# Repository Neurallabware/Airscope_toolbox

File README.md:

<h1 align="center">Airscope</h1>

<p align="center">
  <b>A 1-gram wireless mesoscope for cortex-wide, single-cell-resolution imaging during unrestricted behaviour</b>
</p>

<p align="center">
  <a href="https://airscope.org/devkit/">Device Docs</a> ·
  <a href="https://airscope-docxs.readthedocs.io/en/latest/">Software Docs</a> ·
  <a href="https://drive.google.com/drive/folders/1z9ibX8Ob2NnCdjQDHI7Z4tdhdspn647B?usp=drive_link">Data Release</a>
</p>

---

Airscope is an open hardware and software platform for wireless mesoscopic calcium imaging in freely behaving mice. The device achieves a **6 mm field of view** at ~4 µm lateral resolution, streams or logs **1600 × 1200 px images at 10 Hz**, and weighs approximately **1 g**.

This repository accompanies the manuscript:

> **Deciphering cortex-wide neural dynamics of naturally behaving mice by a 1-gram wireless mesoscope**
> *Zhang et al., Nature, 2025* （Manuscript in preparation）

---

## Repository Structure

| Directory | Description |
|-----------|-------------|
| [`Structure/`](./Structure) | SolidWorks assemblies and part files — housing, baseplate, optical mount, PCB carrier, flexible LED board |
| [`Zemax/`](./Zemax) | Zemax optical design files for the aspheric module |
| [`Electronics/`](./Electronics) | KiCad projects for the main PCB and auxiliary boards |
| [`Firmware/`](./Firmware) | Embedded code for wireless control, camera acquisition, and device configuration |
| [`DAQ_software/`](./DAQ_software) | Python host software and Windows installer for device discovery, preview, and recording |
| [`Software/`](./Software) | Calcium-imaging processing, behavioural segmentation, and neural-decoding pipelines |
| [`Data_release/`](./Data_release) | Example datasets, visualization notebooks, and download instructions |

---

## Key Capabilities

- **Cortex-wide cellular imaging** — 6 mm FOV with single-cell spatial resolution across the dorsal cortex
- **Untethered operation** — wireless data transfer and on-board logging for freely moving, multi-animal, and aquatic paradigms
- **Integrated acquisition stack** — firmware + host software for discovery, preview, timestamping, and recording
- **Reproducible calcium processing** — motion correction → background removal → neuron segmentation → trace extraction
- **Behavioural analysis** — SAM2Mice for multi-animal tracking; Neuron-BERT for decoding social-interaction outcomes

---

## Software Modules

### Calcium-imaging processing · [`Software/Airscope_ca_processing`](./Software/Airscope_ca_processing)

End-to-end pipeline from raw frames to segmented ROI traces. Accepts image sequences, TIFF stacks, and MP4 input; configured with [Hydra](https://hydra.cc) for reproducible batch runs.

```bash
cd Software/Airscope_ca_processing
conda create -n PICO python=3.10 && conda activate PICO
pip install -r requirements.txt && pip install -e .
```

```bash
airscope-process \
  data_path=/path/to/session/frames \
  out_path=/path/to/session/analysis \
  rmbg.gpu_ids=0 rmbg.multi_gpu=false
```

Primary outputs: `seg_results_filtered.mat`, `infer_results_filtered.mat`, `cm_filtered.mat`

---

### SAM2Mice · [`Software/SAM2Mice`](./Software/SAM2Mice)

SAM 2–based mouse segmentation and tracking. Supports manual prompts, YOLOv11 auto-prompts, and bootstrapped inference for videos that exceed GPU memory.

```bash
cd Software/SAM2Mice
pip install torch==2.6.0 torchvision==0.21.0 torchaudio==2.6.0 --index-url https://download.pytorch.org/whl/cu124
pip install -e ".[notebooks]" && python setup.py build_ext --inplace
```

Notebooks in [`Software/SAM2Mice/notebooks_SAM2-MICE`](./Software/SAM2Mice/notebooks_SAM2-MICE) cover basic segmentation, long-video bootstrapping, automatic tracking, and public-dataset examples.

---

### Neuron-BERT · [`Software/Neuron_BERT`](./Software/Neuron_BERT)

Transformer-based decoder for predicting social-interaction outcomes from dual-animal neural activity recordings.

---

### Host acquisition software · [`DAQ_software/`](./DAQ_software)

Dependency-free Python backend — runs without any additional packages:

```bash
cd DAQ_software/airscope_pybackend
python server.py
# UI available at http://127.0.0.1:8765/
```

A packaged Windows installer is also provided at [`DAQ_software/airscope.msi`](./DAQ_software/airscope.msi).

---

## Data Release

Example datasets are hosted on [Google Drive](https://drive.google.com/drive/folders/1z9ibX8Ob2NnCdjQDHI7Z4tdhdspn647B?usp=drive_link) and documented in [`Data_release/README.md`](./Data_release/README.md).
The Google Drive root README is maintained at [`Data_release/README_google_drive.md`](./Data_release/README_google_drive.md) and can be uploaded to Drive as `README_google_drive.md`.

| Dataset | Contents |
|---------|----------|
| Enriched habitat | Calcium traces, multi-view behaviour videos, detection boxes, arena annotations, cortical labels, neuron centroids |
| Multi-animal interaction | Calcium traces, SAM2 instance masks, mouse trajectories, cortical labels, neuron centres |
| MCU timestamp | Frame-rate validation files; use `calculate_frame_rate.ipynb` to verify |
| Optical characterisation | USAF 1951 target images and fluorescent grid slides |

Each dataset directory includes a `README.md` and a `visualize_data.ipynb` notebook.

---

## Requirements

| Component | Environment |
|-----------|-------------|
| Host acquisition software | Python ≥ 3.9, standard library only |
| Calcium processing | Linux, Python 3.10, CUDA-enabled PyTorch recommended |
| SAM2Mice | Python 3.11, PyTorch 2.6.0, CUDA 12.4 |
| Neuron-BERT | Python 3.x, PyTorch, NumPy, scikit-learn, pandas, matplotlib |

See the component-level `README.md` files for exact commands and configuration.

---

## Licensing

Airscope is distributed as a multi-licence repository:

| Material | Licence |
|----------|---------|
| Hardware design (`Structure/`, `Electronics/`, `Zemax/`) | CC-BY-NC-SA-4.0 (commercial use by separate agreement) |
| Software (`DAQ_software/`, `Firmware/`, `Software/`) | GPL-3.0-only |
| Documentation, figures, notebooks, released data | CC-BY-4.0 |

See [`LICENSE`](./LICENSE), [`LICENSES/`](./LICENSES), and [`NOTICE.md`](./NOTICE.md) for the authoritative licence map and third-party notices.

---

## Citation

```bibtex
@article{airscope2025,
  title   = {Deciphering cortex-wide neural dynamics of naturally
             behaving mice by a 1-gram wireless mesoscope},
  author  = {Zhang, Yuanlong and Li, Angran and Yuan, Lekang and
             Wang, Mingrui and Zhao, Weihao and Wang, Zhenbo and
             Zang, Boyang and Zhou, Yangxuan and Yu, Tao and Gao, Lin
             and Wu, Yu and Zhu, Rongkang and Tian, Mengyi and Li, Kun
             and Wu, Jiamin and Dai, Pu and Dai, Qionghai},
  journal = {Nature},
  year    = {2025},
  note    = {Manuscript in preparation}
}
```

## Documentation

- Device assembly, acquisition, and operation: <https://airscope.org/devkit/>
- Processing pipelines, notebooks, and examples: <https://airscope-docxs.readthedocs.io/en/latest/>

## Contact

Questions, bug reports, and suggestions can be submitted via the issue tracker or sent to the corresponding authors listed in the manuscript.

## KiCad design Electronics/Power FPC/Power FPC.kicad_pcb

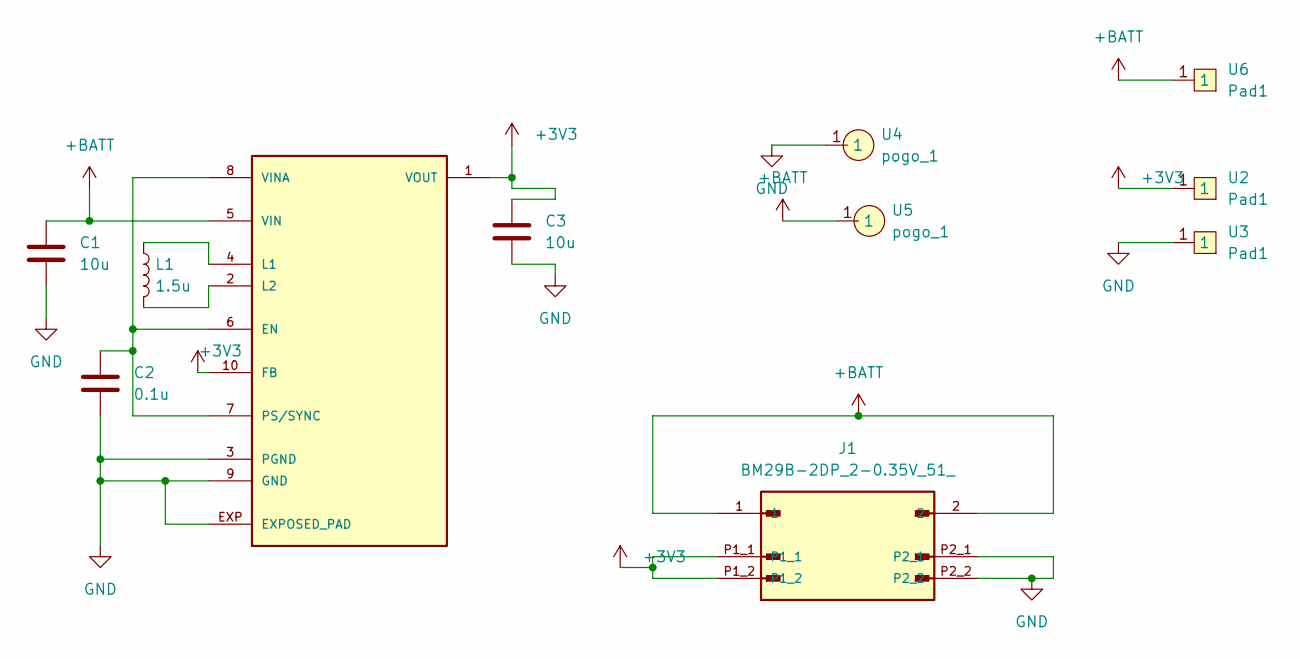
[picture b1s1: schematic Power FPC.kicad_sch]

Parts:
C1, C3: 10u; C_0603_Metric
C2: 0.1u; C_0402_Metric
J1: BM29B-2DP_2-0.35V_51_; BM29B-2DP_2-0.35V_51__HRS_BM29B-2DP_2-0.35V_51_; PARTREV 20210716
L1: 1.5u; ASIC-0805F
U1: TPS63031; TPS63031-10SON
U2, U3, U6: Pad1; Rec_Pad_1
U4, U5: pogo_1

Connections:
+3V3: C3.1, J1.P1_1, J1.P1_2, U1.1 (VOUT), U1.10 (FB), U2.1
+BATT: C1.1, J1.1, J1.2, U1.5 (VIN), U5.1, U6.1
GND: C1.2, C2.2, C3.2, J1.P2_1, J1.P2_2, U1.3 (PGND), U1.9 (GND), U1.EXP (EXPOSED_PAD), U3.1, U4.1
unnamed: C2.1, U1.6 (EN), U1.7 (PS/SYNC), U1.8 (VINA)
unnamed: L1.1, U1.4 (L1)
unnamed: L1.2, U1.2 (L2)

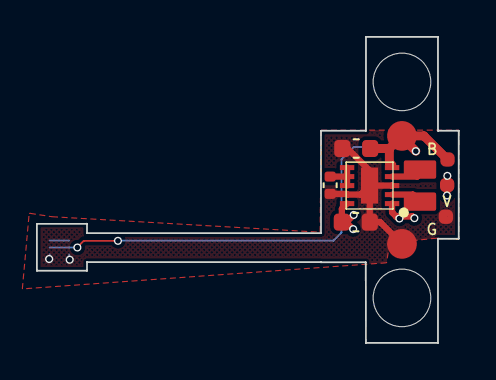
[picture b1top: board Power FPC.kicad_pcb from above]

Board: 2 copper layers, 23.4 x 17.0 mm, 11 parts (1 on the bottom side), 6 nets.

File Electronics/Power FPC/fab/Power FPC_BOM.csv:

"Comment","Description","Designator","Footprint","LibRef","Pins","Quantity","PartNumber","url",
"10u","desc","C1,C3,","C_0603_Metric","libref","2","2","","",
"0.1u","desc","C2,","C_0402_Metric","libref","2","1","","",
"1.5u","desc","L1,","ASIC-0805F","libref","2","1","","",
"TPS63031","desc","U1,","TPS63031-10SON","libref","11","1","","",
"Pad1","desc","U2,U3,U6,","Rec_Pad_1","libref","1","3","","",
"pogo_1","desc","U4,U5,","pogo_1","libref","1","2","","",
"BM29B-2DP_2-0.35V_51_","desc","J1,","BM29B-2DP_2-0.35V_51__HRS_BM29B-2DP_2-0.35V_51_","libref","6","1","","",

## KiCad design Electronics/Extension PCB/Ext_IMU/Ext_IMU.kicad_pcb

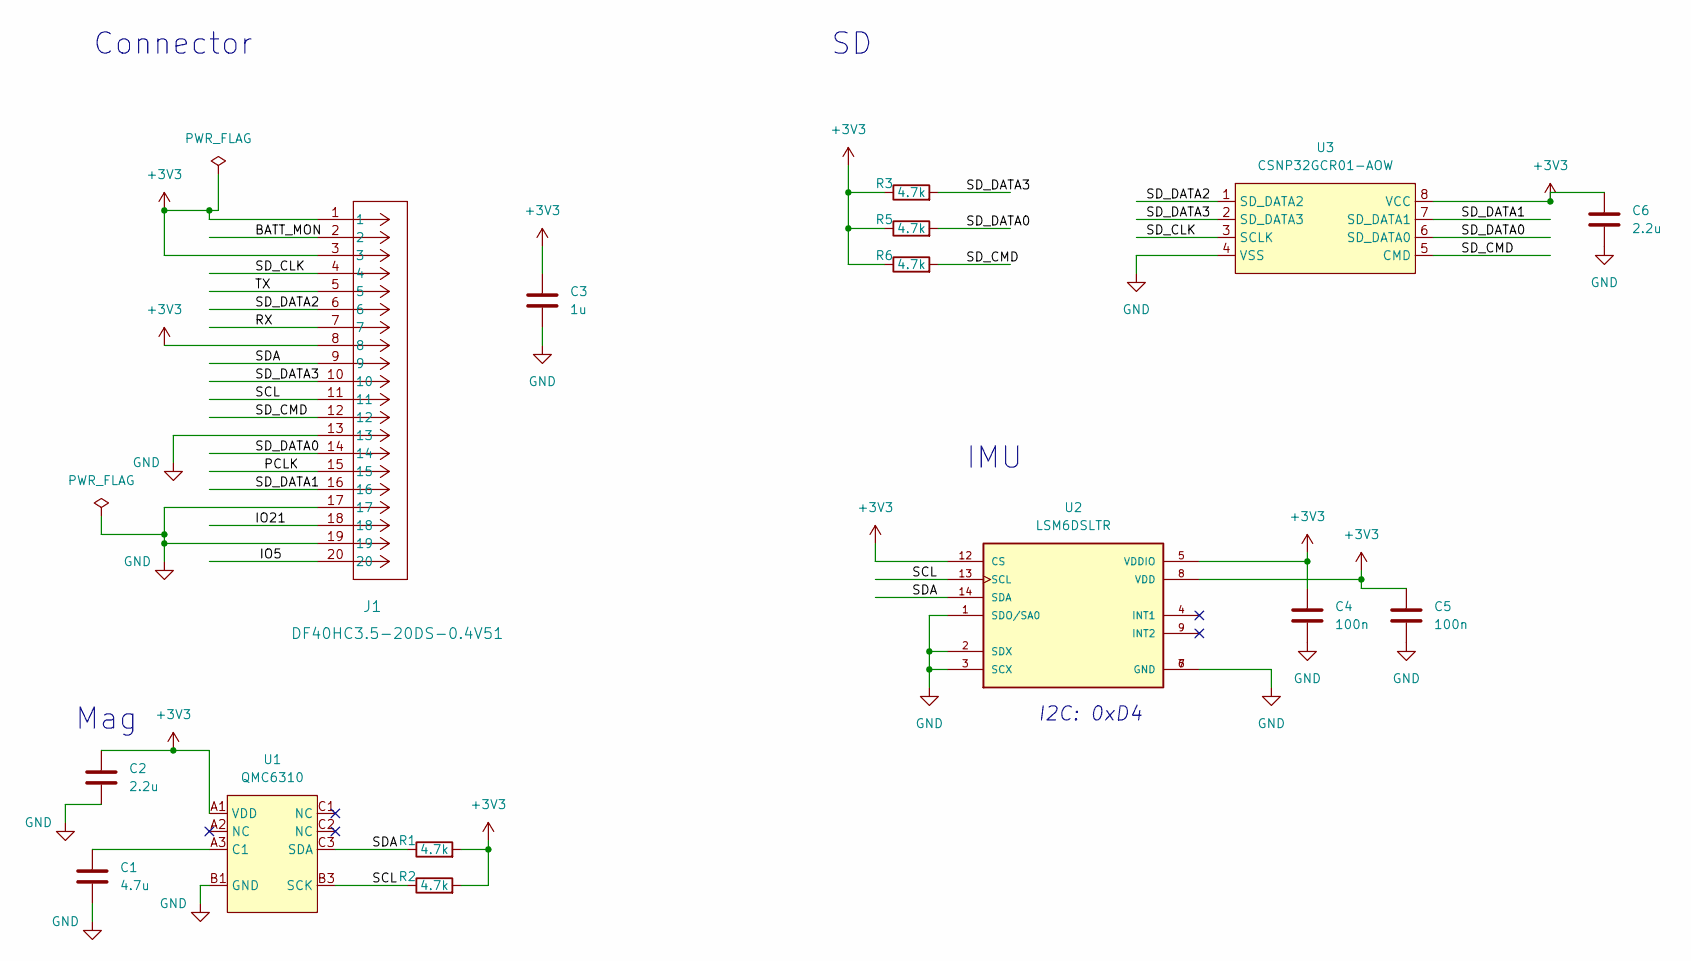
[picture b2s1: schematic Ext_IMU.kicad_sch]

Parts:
C1: 4.7u; C_0201_Metric
C2, C6: 2.2u; C_0201_Metric
C3: 1u; C_0402_Metric
C4, C5: 100n; C_0201_Metric
J1: DF40HC3.5-20DS-0.4V51; CONN20_DF40HC_HIR
R1, R2, R3, R5, R6: 4.7k; R_0201_Metric
U1: QMC6310
U2: LSM6DSLTR; LSM6DSLTR_PQFN50P300X250X86-14N; PARTREV 7
U3: CSNP32GCR01-AOW; SD_NAND_32

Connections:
+3V3: C2.1, C3.1, C4.1, C5.1, C6.1, J1.1, J1.3, J1.8, R1.2, R2.2, R3.1, R5.1, R6.1, U1.A1 (VDD), U2.5 (VDDIO), U2.8 (VDD), U2.12 (CS), U3.8 (VCC)
/BATT_MON: J1.2
/IO5: J1.20
/IO21: J1.18
/PCLK: J1.15
/RX: J1.7
/SCL: J1.11, R2.1, U1.B3 (SCK), U2.13 (SCL)
/SDA: J1.9, R1.1, U1.C3 (SDA), U2.14 (SDA)
/SD_CLK: J1.4, U3.3 (SCLK)
/SD_CMD: J1.12, R6.2, U3.5 (CMD)
/SD_DATA0: J1.14, R5.2, U3.6 (SD_DATA0)
/SD_DATA1: J1.16, U3.7 (SD_DATA1)
/SD_DATA2: J1.6, U3.1 (SD_DATA2)
/SD_DATA3: J1.10, R3.2, U3.2 (SD_DATA3)
/TX: J1.5
GND: C1.2, C2.2, C3.2, C4.2, C5.2, C6.2, J1.13, J1.17, J1.19, U1.B1 (GND), U2.1 (SDO/SA0), U2.2 (SDX), U2.3 (SCX), U2.6 (GND), U2.7 (GND), U3.4 (VSS)
unnamed: C1.1, U1.A3 (C1)

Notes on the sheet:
I2C: 0xD4
IMU
Mag
Connector

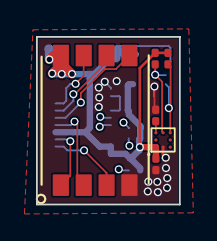
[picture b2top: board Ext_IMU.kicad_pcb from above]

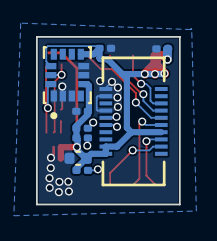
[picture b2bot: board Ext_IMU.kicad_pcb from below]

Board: 4 copper layers, 7.9 x 9.3 mm, 15 parts (9 on the bottom side), 11 nets.

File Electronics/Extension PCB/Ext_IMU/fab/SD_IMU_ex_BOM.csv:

"Comment","Description","Designator","Footprint","LibRef","Pins","Quantity","PartNumber","url",
"4.7u","desc","C1,","C_0201_Metric","libref","4","1","","",
"2.2u","desc","C2,","C_0201_Metric","libref","4","1","","",
"4.7k","desc","R1,R2,","R_0201_Metric","libref","4","2","","",
"QMC6310","desc","U1,","QMC6310","libref","8","1","","",
"CSNP32GCR01-AOW","desc","U3,","SD_NAND_32","libref","8","1","","",
"1u","desc","C3,","C_0402_Metric","libref","2","1","","",
"100n","desc","C4,C5,","C_0201_Metric","libref","4","2","","",
"2.2u","desc","C6,","C_0201_Metric","libref","4","1","","",
"DF40HC3.5-20DS-0.4V51","desc","J1,","CONN20_DF40HC_HIR","libref","20","1","","",
"4.7k","desc","R3,R5,R6,","R_0201_Metric","libref","4","3","","",
"LSM6DSLTR","desc","U2,","LSM6DSLTR_PQFN50P300X250X86-14N","libref","14","1","","",

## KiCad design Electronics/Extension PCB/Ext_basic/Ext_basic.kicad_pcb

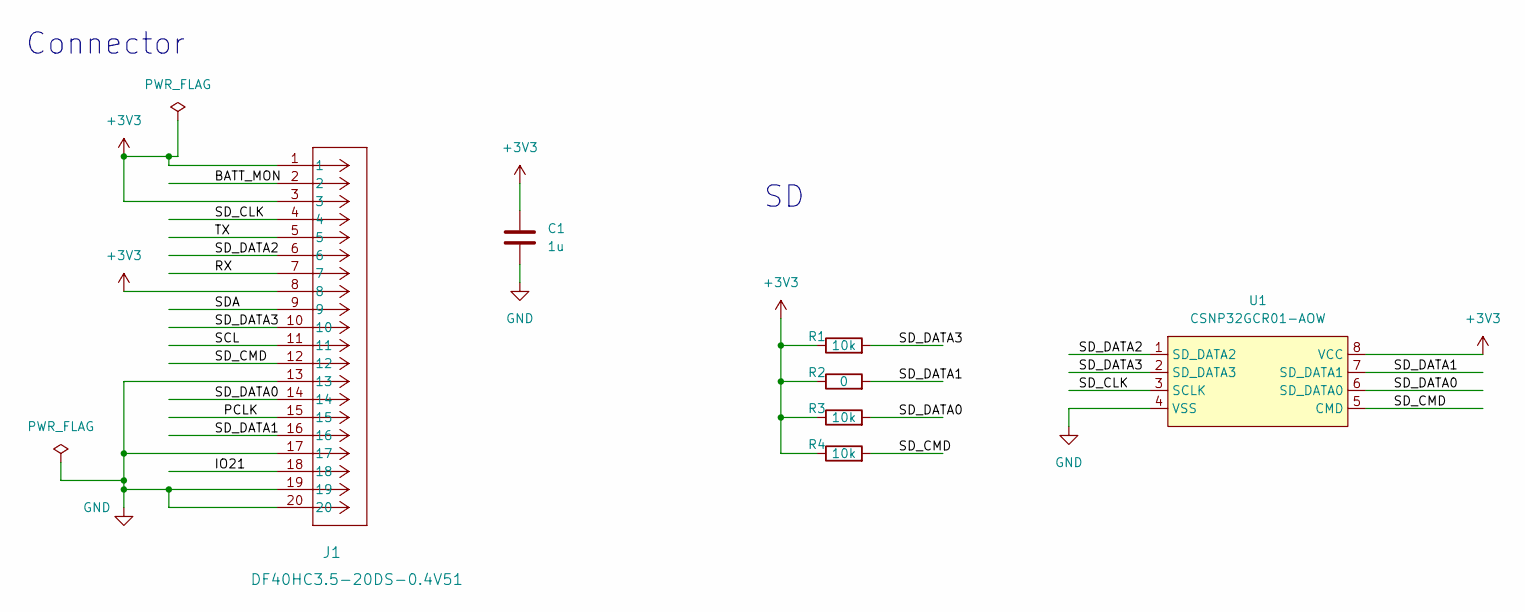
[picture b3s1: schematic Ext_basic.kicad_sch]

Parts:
C1: 1u; C_0402_Metric
J1: DF40HC3.5-20DS-0.4V51; CONN20_DF40HC_HIR
R1, R3, R4: 10k; R_0201_Metric
R2: 0; R_0201_Metric
U1: CSNP32GCR01-AOW; SD_NAND_32

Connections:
+3V3: C1.1, J1.1, J1.3, J1.8, R1.1, R2.1, R3.1, R4.1, U1.8 (VCC)
/BATT_MON: J1.2
/IO21: J1.18
/PCLK: J1.15
/RX: J1.7
/SCL: J1.11
/SDA: J1.9
/SD_CLK: J1.4, U1.3 (SCLK)
/SD_CMD: J1.12, R4.2, U1.5 (CMD)
/SD_DATA0: J1.14, R3.2, U1.6 (SD_DATA0)
/SD_DATA1: J1.16, R2.2, U1.7 (SD_DATA1)
/SD_DATA2: J1.6, U1.1 (SD_DATA2)
/SD_DATA3: J1.10, R1.2, U1.2 (SD_DATA3)
/TX: J1.5
GND: C1.2, J1.13, J1.17, J1.19, J1.20, U1.4 (VSS)

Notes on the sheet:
Connector

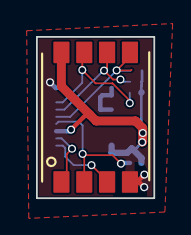
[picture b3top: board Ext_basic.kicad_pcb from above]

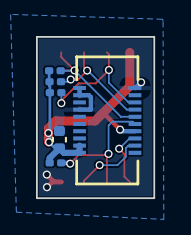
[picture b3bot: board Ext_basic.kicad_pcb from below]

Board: 2 copper layers, 6.5 x 9.0 mm, 7 parts (6 on the bottom side), 8 nets.

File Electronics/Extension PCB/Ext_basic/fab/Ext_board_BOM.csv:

"Comment","Description","Designator","Footprint","LibRef","Pins","Quantity","PartNumber","url",
"CSNP32GCR01-AOW","desc","U1,","SD_NAND_32","libref","8","1","","",
"1u","desc","C1,","C_0402_Metric","libref","2","1","","",
"DF40HC3.5-20DS-0.4V51","desc","J1,","CONN20_DF40HC_HIR","libref","20","1","","",
"10k","desc","R1,R3,R4,","R_0201_Metric","libref","4","3","","",
"0","desc","R2,","R_0201_Metric","libref","4","1","","",

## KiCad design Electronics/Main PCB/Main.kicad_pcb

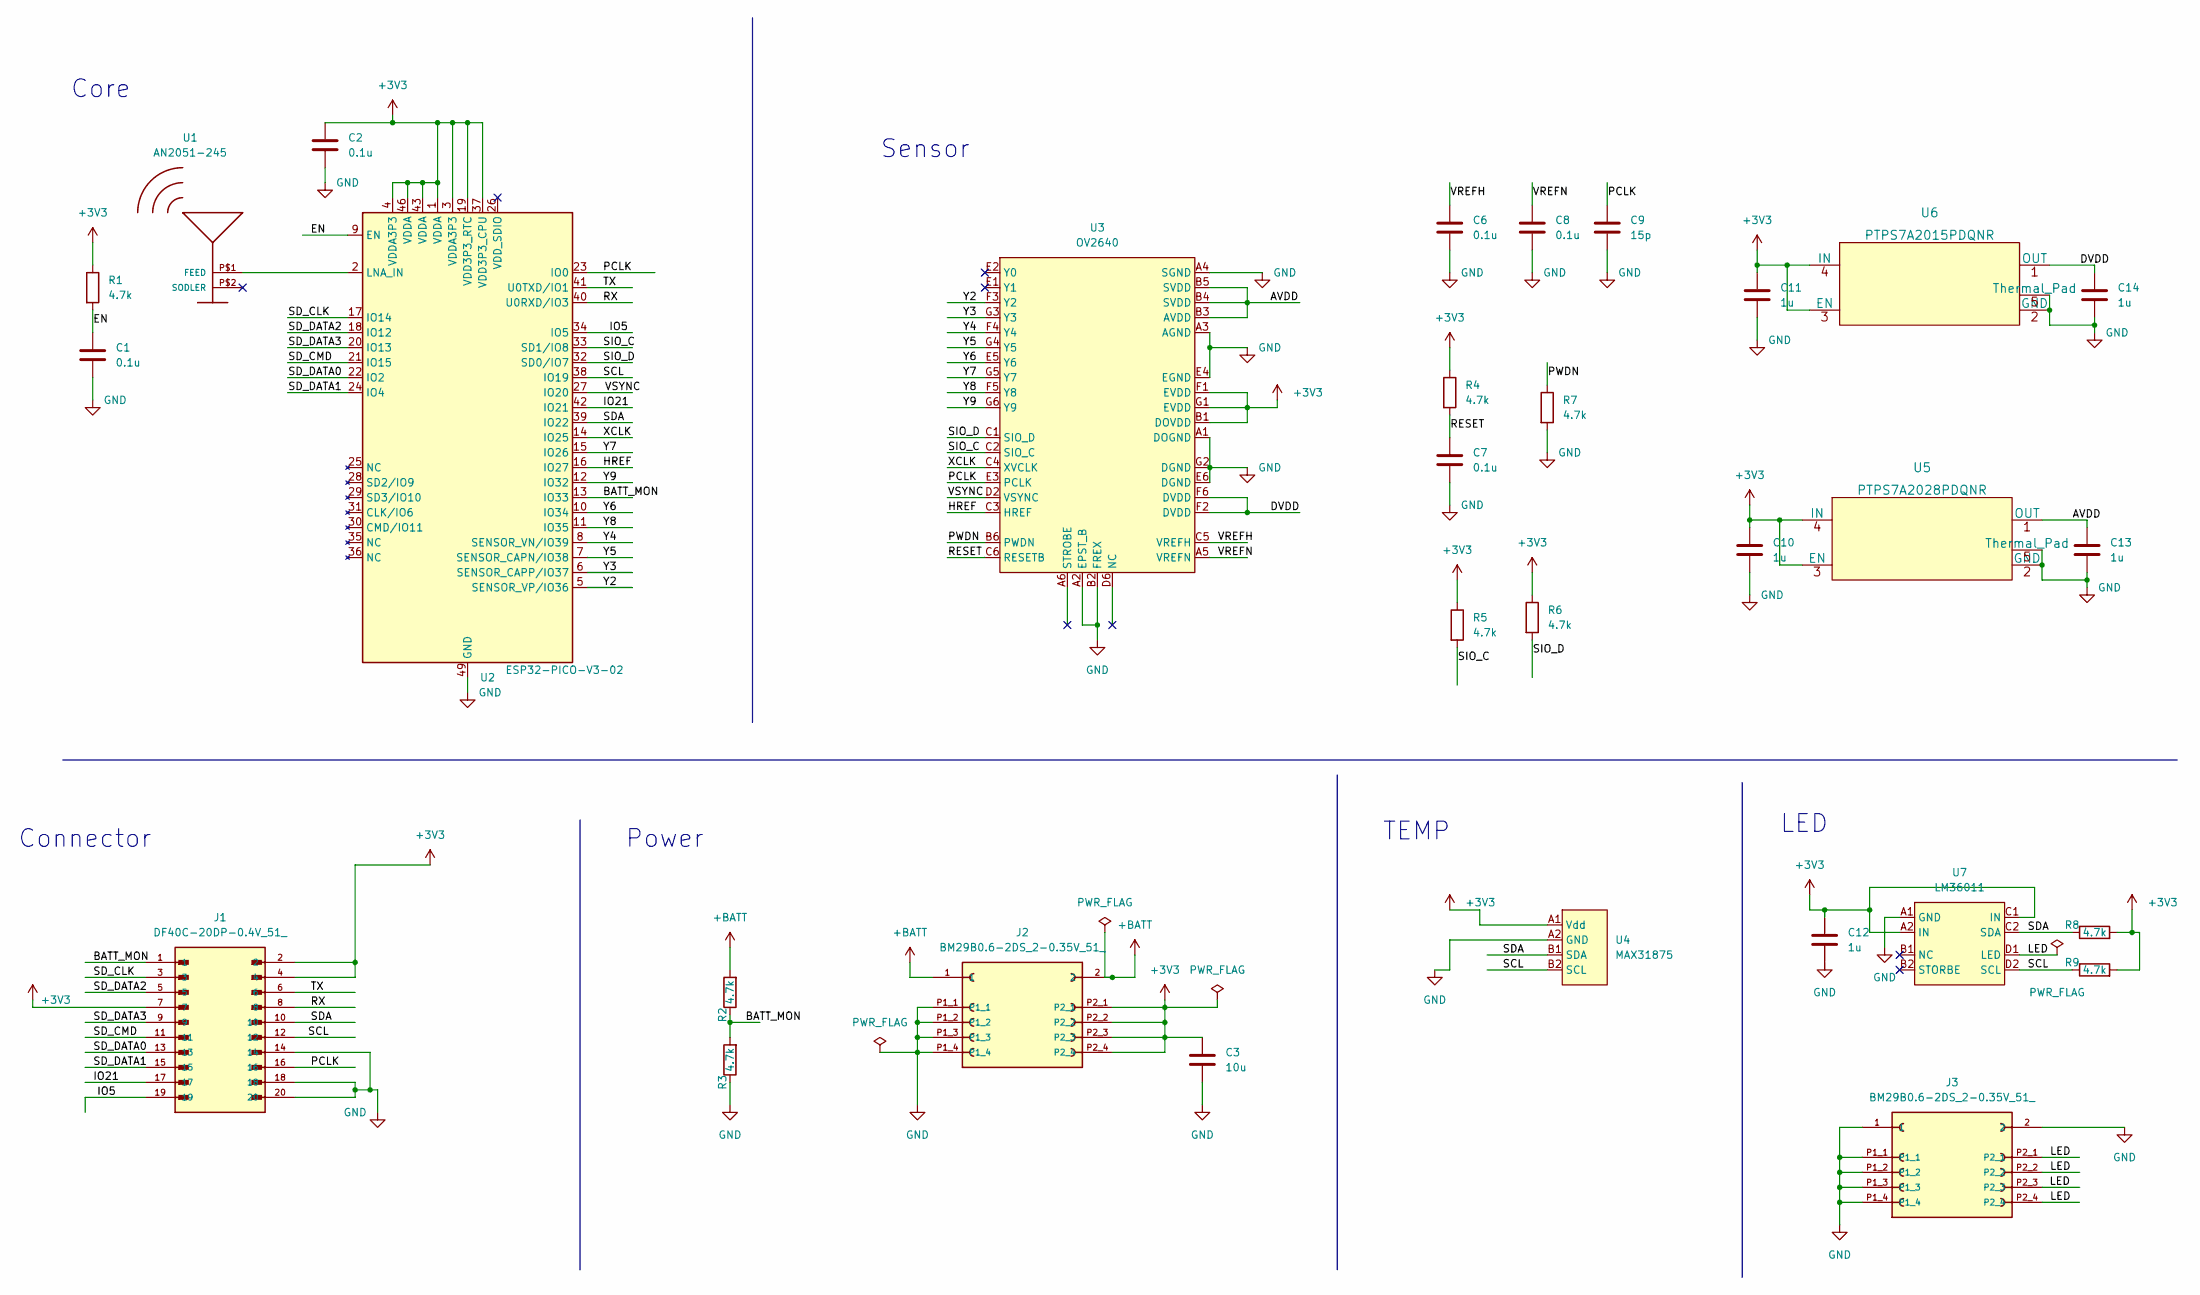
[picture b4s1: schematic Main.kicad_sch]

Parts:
C1, C2, C6, C7, C8: 0.1u; C_0201_Metric
C3: 10u; C_0603_Metric
C9: 15p; C_0201_Metric
C10, C11, C12, C13, C14: 1u; C_0201_Metric
J1: DF40C-20DP-0.4V_51_; HRS_DF40C-20DP-0.4V_51_; PARTREV 02/2020
J2, J3: BM29B0.6-2DS_2-0.35V_51_; BM29B0.6-2DS_2-0.35V_51__HRS_BM29B0.6-2DS_2-0.35V_51_; PARTREV 20210414
R1, R2, R3, R4, R5, R6, R7, R8, R9: 4.7k; R_0201_Metric
U1: AN2051-245; AN2051
U2: ESP32-PICO-V3-02; Pico-QFN-48
U3: OV2640; OV2640_BGA38
U4: MAX31875; BGA4N40P2X2_83X83X37N
U5: PTPS7A2028PDQNR; PTPS7A20185PDQNR
U6: PTPS7A2015PDQNR; PTPS7A20185PDQNR
U7: LM36011; LM36011_BGA24

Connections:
+3V3: C2.1, C3.1, C10.1, C11.1, C12.1, J1.2, J1.4, J1.7, J2.P2_1, J2.P2_2, J2.P2_3, J2.P2_4, R1.1, R4.1, R5.1, R6.1, R8.2, R9.2, U2.1 (VDDA), U2.3 (VDDA3P3), U2.4 (VDDA3P3), U2.19 (VDD3P3_RTC), U2.37 (VDD3P3_CPU), U2.43 (VDDA), U2.46 (VDDA), U3.B1 (DOVDD), U3.F1 (EVDD), U3.G1 (EVDD), U4.A1 (Vdd), U5.3 (EN), U5.4 (IN), U6.3 (EN), U6.4 (IN), U7.A2 (IN), U7.C1 (IN)
+BATT: J2.1, J2.2, R2.2
/AVDD: C13.1, U3.B3 (AVDD), U3.B4 (SVDD), U3.B5 (SVDD), U5.1 (OUT)
/BATT_MON: J1.1, R2.1, R3.2, U2.13 (IO33)
/DVDD: C14.1, U3.F2 (DVDD), U3.F6 (DVDD), U6.1 (OUT)
/EN: C1.1, R1.2, U2.9 (EN)
/HREF: U2.16 (IO27), U3.C3 (HREF)
/IO5: J1.19, U2.34 (IO5)
/IO21: J1.17, U2.42 (IO21)
/LED: J3.P2_1, J3.P2_2, J3.P2_3, J3.P2_4, U7.D1 (LED)
/PCLK: C9.1, J1.16, U2.23 (IO0), U3.E3 (PCLK)
/PWDN: R7.1, U3.B6 (PWDN)
/RESET: C7.1, R4.2, U3.C6 (RESETB)
/RX: J1.8, U2.40 (U0RXD/IO3)
/SCL: J1.12, R9.1, U2.38 (IO19), U4.B2 (SCL), U7.D2 (SCL)
/SDA: J1.10, R8.1, U2.39 (IO22), U4.B1 (SDA), U7.C2 (SDA)
/SD_CLK: J1.3, U2.17 (IO14)
/SD_CMD: J1.11, U2.21 (IO15)
/SD_DATA0: J1.13, U2.22 (IO2)
/SD_DATA1: J1.15, U2.24 (IO4)
/SD_DATA2: J1.5, U2.18 (IO12)
/SD_DATA3: J1.9, U2.20 (IO13)
/SIO_C: R5.2, U2.33 (SD1/IO8), U3.C2 (SIO_C)
/SIO_D: R6.2, U2.32 (SD0/IO7), U3.C1 (SIO_D)
/TX: J1.6, U2.41 (U0TXD/IO1)
/VREFH: C6.1, U3.C5 (VREFH)
/VREFN: C8.1, U3.A5 (VREFN)
/VSYNC: U2.27 (IO20), U3.D2 (VSYNC)
/XCLK: U2.14 (IO25), U3.C4 (XVCLK)
/Y2: U2.5 (SENSOR_VP/IO36), U3.F3 (Y2)
/Y3: U2.6 (SENSOR_CAPP/IO37), U3.G3 (Y3)
/Y4: U2.8 (SENSOR_VN/IO39), U3.F4 (Y4)
/Y5: U2.7 (SENSOR_CAPN/IO38), U3.G4 (Y5)
/Y6: U2.10 (IO34), U3.E5 (Y6)
/Y7: U2.15 (IO26), U3.G5 (Y7)
/Y8: U2.11 (IO35), U3.F5 (Y8)
/Y9: U2.12 (IO32), U3.G6 (Y9)
GND: C1.2, C2.2, C3.2, C6.2, C7.2, C8.2, C9.2, C10.2, C11.2, C12.2, C13.2, C14.2, J1.14, J1.18, J1.20, J2.P1_1, J2.P1_2, J2.P1_3, J2.P1_4, J3.1, J3.2, J3.P1_1, J3.P1_2, J3.P1_3, J3.P1_4, R3.1, R7.2, U2.49 (GND), U3.A1 (DOGND), U3.A2 (EPST_B), U3.A3 (AGND), U3.A4 (SGND), U3.B2 (FREX), U3.E4 (EGND), U3.E6 (DGND), U3.G2 (DGND), U4.A2 (GND), U5.2 (GND), U5.5 (Thermal_Pad), U6.2 (GND), U6.5 (Thermal_Pad), U7.A1 (GND)
unnamed: U1.P$1 (FEED), U2.2 (LNA_IN)

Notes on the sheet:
Sensor
Power
TEMP
Connector
LED
Core

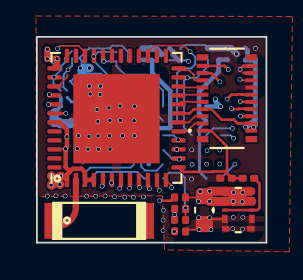
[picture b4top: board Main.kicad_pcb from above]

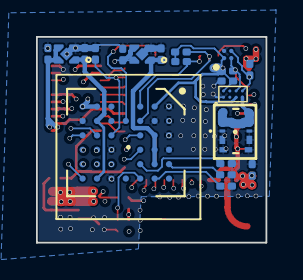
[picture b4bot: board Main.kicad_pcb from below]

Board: 6 copper layers, 12.8 x 11.4 mm, 31 parts (20 on the bottom side), 39 nets.

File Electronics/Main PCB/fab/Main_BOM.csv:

"Comment","Description","Designator","Footprint","LibRef","Pins","Quantity","PartNumber","url",
"0.1u","desc","C1,C7,","C_0201_Metric","libref","4","2","","",
"10u","desc","C3,","C_0603_Metric","libref","2","1","","",
"DF40C-20DP-0.4V_51_","desc","J1,","HRS_DF40C-20DP-0.4V_51_","libref","24","1","","",
"BM29B0.6-2DS_2-0.35V_51_","desc","J2,","BM29B0.6-2DS_2-0.35V_51__HRS_BM29B0.6-2DS_2-0.35V_51_","libref","10","1","","",
"4.7k","desc","R1,R2,R3,R4,","R_0201_Metric","libref","4","4","","",
"AN2051-245","desc","U1,","AN2051","libref","2","1","","",
"ESP32-PICO-V3-02","desc","U2,","Pico-QFN-48","libref","65","1","","",
"0.1u","desc","C2,C6,C8,","C_0201_Metric","libref","4","3","","",
"15p","desc","C9,","C_0201_Metric","libref","4","1","","",
"1u","desc","C10,C11,C12,C13,C14,","C_0201_Metric","libref","4","5","","",
"BM29B0.6-2DS_2-0.35V_51_","desc","J3,","BM29B0.6-2DS_2-0.35V_51__HRS_BM29B0.6-2DS_2-0.35V_51_","libref","10","1","","",
"4.7k","desc","R5,R6,R7,R8,R9,","R_0201_Metric","libref","4","5","","",
"OV2640","desc","U3,","OV2640_BGA38","libref","38","1","","",
"MAX31875","desc","U4,","BGA4N40P2X2_83X83X37N","libref","4","1","","",
"PTPS7A2028PDQNR","desc","U5,","PTPS7A20185PDQNR","libref","5","1","","",
"PTPS7A2015PDQNR","desc","U6,","PTPS7A20185PDQNR","libref","5","1","","",
"LM36011","desc","U7,","LM36011_BGA24","libref","8","1","","",

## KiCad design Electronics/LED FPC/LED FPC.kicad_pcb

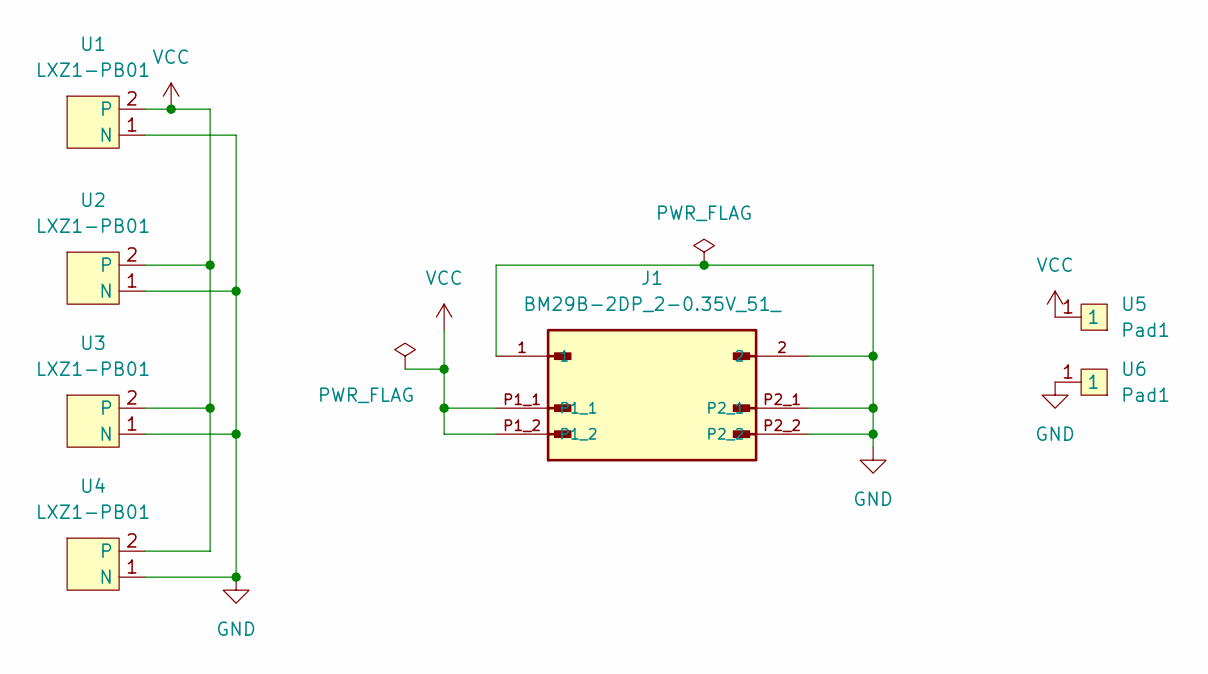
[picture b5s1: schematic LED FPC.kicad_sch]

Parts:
J1: BM29B-2DP_2-0.35V_51_; BM29B-2DP_2-0.35V_51__HRS_BM29B-2DP_2-0.35V_51_; PARTREV 20210716
U1, U2, U3, U4: LXZ1-PB01
U5, U6: Pad1; Rec_Pad_1

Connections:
GND: J1.1, J1.2, J1.P2_1, J1.P2_2, U1.1 (N), U2.1 (N), U3.1 (N), U4.1 (N), U6.1
VCC: J1.P1_1, J1.P1_2, U1.2, U2.2, U3.2, U4.2, U5.1

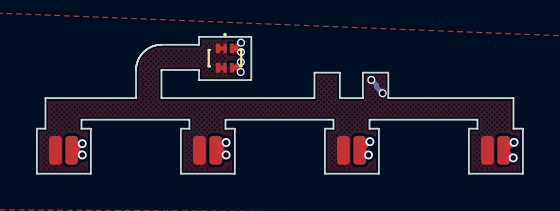
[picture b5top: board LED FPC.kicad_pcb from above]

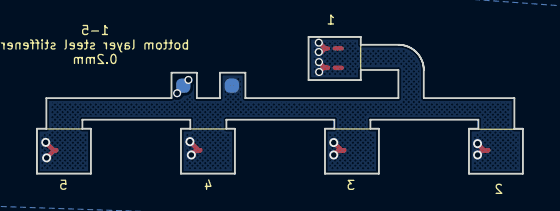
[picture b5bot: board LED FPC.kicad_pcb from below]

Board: 2 copper layers, 27.0 x 7.6 mm, 7 parts (2 on the bottom side), 2 nets.

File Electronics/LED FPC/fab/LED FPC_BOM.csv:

"Comment","Description","Designator","Footprint","LibRef","Pins","Quantity","PartNumber","url",
"BM29B-2DP_2-0.35V_51_","desc","J1,","BM29B-2DP_2-0.35V_51__HRS_BM29B-2DP_2-0.35V_51_","libref","6","1","","",
"LXZ1-PB01","desc","U1,U2,U3,U4,","LXZ1-PB01","libref","2","4","","",
"Pad1","desc","U5,U6,","Rec_Pad_1","libref","1","2","","",

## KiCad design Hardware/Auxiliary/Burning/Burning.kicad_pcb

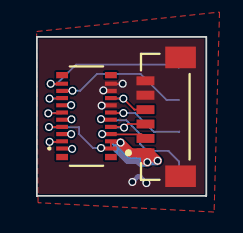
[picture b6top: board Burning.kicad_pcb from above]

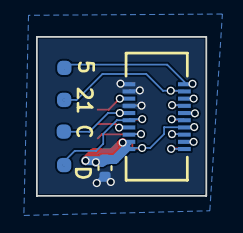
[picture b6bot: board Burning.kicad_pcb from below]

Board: 2 copper layers, 9.4 x 8.8 mm, 8 parts (6 on the bottom side), 16 nets.

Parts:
C1: 1u; C_0402_Metric
J1: DF40C-20DP-0.4V_51_; HRS_DF40C-20DP-0.4V_51_
J2: SM06B-SURS-TF(LF)(SN); JST_SM06B-SURS-TF(LF)(SN)
J3: DF40HC3.5-20DS-0.4V51; CONN20_DF40HC_HIR
U1, U2, U3, U4: Pad1; Rec_Pad_1

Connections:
+3V3: C1.1, J1.2, J1.4, J1.7, J2.1, J3.1, J3.3, J3.8
/BATT_MON: J1.1, J3.2
/IO5: J1.19, J3.20, U2.1
/IO21: J1.17, J3.18, U1.1
/PCLK: J1.16, J2.4, J3.15
/RX: J1.8, J2.3, J3.7
/SCL: J1.12, J3.11, U4.1
/SDA: J1.10, J3.9, U3.1
/SD_CLK: J1.3, J3.4
/SD_CMD: J1.11, J3.12
/SD_DATA0: J1.13, J3.14
/SD_DATA1: J1.15, J3.16
/SD_DATA2: J1.5, J3.6
/SD_DATA3: J1.9, J3.10
/TX: J1.6, J2.2, J3.5
GND: C1.2, J1.14, J1.18, J1.20, J2.5, J2.6, J2.S1 (SHIELD), J2.S2 (SHIELD), J3.13, J3.17, J3.19

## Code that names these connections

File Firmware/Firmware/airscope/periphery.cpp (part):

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    config.pin_d5 = Y7_GPIO_NUM;
    config.pin_d6 = Y8_GPIO_NUM;
    config.pin_d7 = Y9_GPIO_NUM;
    config.pin_xclk = XCLK_GPIO_NUM;
    config.pin_pclk = PCLK_GPIO_NUM;
    config.pin_vsync = VSYNC_GPIO_NUM;
    config.pin_href = HREF_GPIO_NUM;
    config.pin_sccb_sda = SIOD_GPIO_NUM;
    config.pin_sccb_scl = SIOC_GPIO_NUM;
    config.pin_pwdn = PWDN_GPIO_NUM;
    config.pin_reset = RESET_GPIO_NUM;

    config.xclk_freq_hz = 16000000;
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
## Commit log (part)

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2025-09-24 0924 update
2025-09-25 Airscope design documents
2025-09-25 Add main page
2025-09-25 Modify link
2025-11-14 update software
2026-05-16 update ca processing
2026-05-16 Release multi animal and large habitat
2026-05-20 release MCU timestamps
2026-05-24 Update README to remove code availability information
    Removed code availability section and related links from README.
2026-05-27 upload zemax
2026-05-28 Modify headings for Electronics and Firmware sections
    Updated section headings in README for clarity.
2026-05-28 Update data release section with link to Google Drive
    Added link to full data release in the Data Release section.
2026-05-29 add optical characteristic data and add readme
2026-05-29 add readme
2026-05-29 docs: update Airscope release overview
2026-05-29 docs: update data release metadata
2026-05-29 firmware: reorganize Airscope firmware
2026-05-29 hardware: move electronics designs into Electronics
2026-05-29 cad: reorganize mechanical and optical design files
2026-05-29 software: add Airscope DAQ software
2026-05-29 sam2mice: update segmentation pipeline and docs
2026-05-29 SAM2Mice updata notebook
2026-05-30 docs: add release licensing metadata
2026-05-30 docs: formalize Airscope README
2026-05-30 Center images at 50% width in Neuron_BERT README
2026-05-30 license: use GPL-3.0 for software
2026-06-01 modify grammer muiti

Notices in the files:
parts and their libraries:
Copyright 2021 Accelerated Designs. All rights reserved.
